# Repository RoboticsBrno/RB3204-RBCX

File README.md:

# RB3204-RBCX

<p align="center">

</p>

RBCX is a universal controller for hobby robots. It is a successor of [RB3201-RBControl](https://github.com/RoboticsBrno/RB3201-RBControl).
It is used in our robot [Robotka](https://robotka.robotickytabor.cz) on [Robo camp 2020](https://robotickytabor.cz).

<div align="center">
  	<td></td>
	<td></td>
</div>

## Features
- 4 DC motors with encoders
- 4 servos with feedback (via ADC)
- 4 LEDs
- buttons with the gamepad interface
- Smart Servo connector
- piezo buzzer
- RTC
- ultra-sonic distance sensor connector
- I2C connectors
- OLED display connector
- accelerometer and gyroscope
- micro USB and USB-C connectors
- battery connector (without charging circuit)

## Hardware
Board is based on `STM32F103VC` microcontroller and `ESP32-DevKitC`.

STM32 is used for motor control and other low-level tasks.
ESP32 is used for high-level tasks like communication with mobile app and sending commands to STM32 via UART.

### [STM32F103VC](https://www.st.com/en/microcontrollers-microprocessors/stm32f103vc.html)

-  72 MHz, 32bit ARM Cortex-M3
-  48 KiB RAM, 256 KiB Flash
-  5x UART, USB
-  Debug support (with ST-Link)
-  Programmable in C++, with FreeRTOS and stm32cube framework, in Platform.io
-  Our [bootloader](https://github.com/RoboticsBrno/sboot_stm32) based on [sboot_stm32](https://github.com/dmitrystu/sboot_stm32).

### [ESP32-DevKitC](https://www.espressif.com/en/products/devkits/esp32-devkitc)

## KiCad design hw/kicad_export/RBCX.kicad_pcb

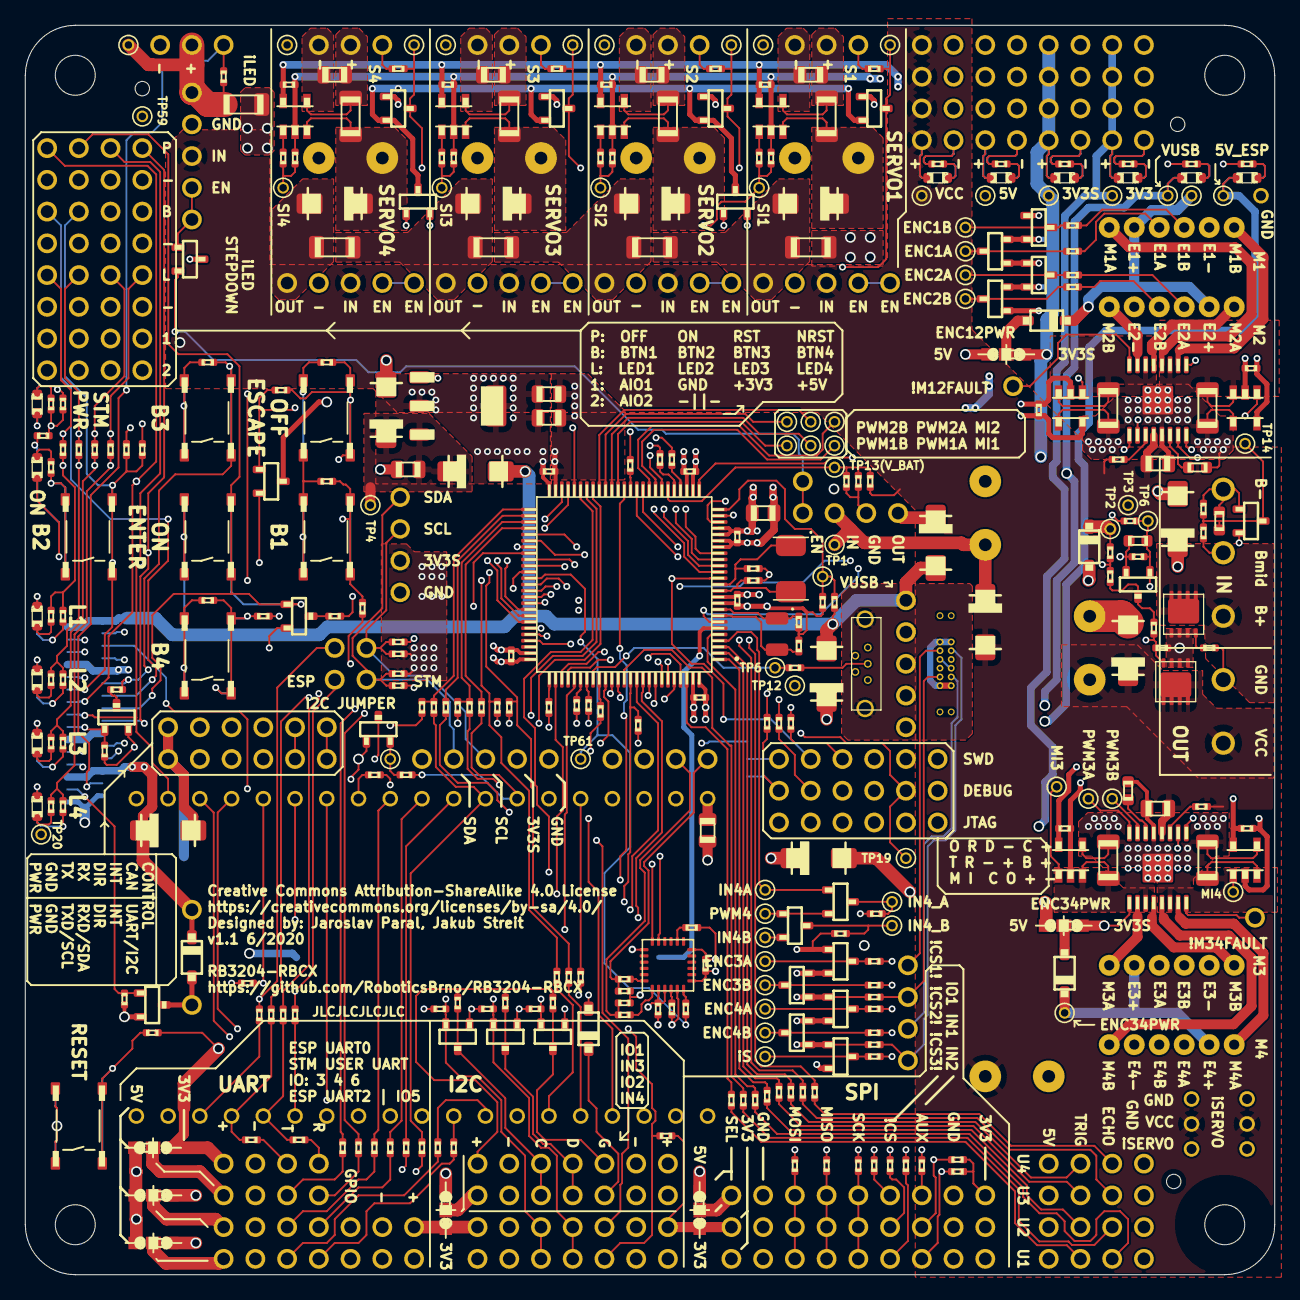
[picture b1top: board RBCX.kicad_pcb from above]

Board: 4 copper layers, 100.0 x 100.0 mm, 470 parts (0 on the bottom side), 294 nets.

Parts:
@HOLE0, @HOLE1, @HOLE2, @HOLE3, @HOLE4, @HOLE5, @HOLE6: (no value)
B1: PIEZO
BAT1: CR2032; SMD-BAT-CR2032-BS-6-1
C1, C2, C24, C25, C26, C27, C40: 220u; E5-10,5
C3, C4, C14, C19, C36, C37, C38, C39, C41, C51, C53: 10u; C0805
C5, C17, C18, C22, C23, C28, C29, C30, C31, C43, C44, C46, C47, C48, C49, C50, C52: 100n; C0402
C6, C8, C16, C21: 2u2; C0603
C7, C9, C10, C11, C12, C13, C32, C33, C34, C35: 1u; C0402
C15, C20, C42: 10n; C0402
C45: 2n2; C0402
C54, C56: 18p; C0402
C55, C57: 6.8p; C0402
D1, D10, D14, D15, D20: B5819W; SOD123
D2, D3, D4, D5, D6, D7, D8, D12, D29, D30, D31, D32, D38: SS34; SMA
D9, D16, D17, D18, D19, D22, D23, D24, D25, D33, D34, D35, D36, D37: BAS40-04; SOT23
D11, D13, D21, D26, D27, D28: BAS40-05; SOT23
IC1: AMS1117-3.3; SOT223
IC2, IC5: DRV8833PWP; HTSSOP
IC3, IC4, IC6, IC7, IC8, IC9, IC10, IC11: INA180A4; SOT23-5L
IC12: MPU-6050; QFN50P400X400X95-24N
IC13: STM32F103VCT6; QFP50P1600X1600X160-100N_STM32F103VCT6
IM1, IM2, IM5, IM6, IM7, IM8: STEPDOWN
IM3: DISPLAY-OLED-128X64-I2C-W_HOLES; DISPLAY-OLED-128X64-I2C_W-HOLES
IM4: DISPLAY-OLED-128X32
IM9: DEVKITC
JP1: 3V3_EN; 1X01
JP2: +3V3STM; 2X04
JP3: +3V3; 2X04
JP4: +5V; 2X04
JP5: VCC; 2X04
JP6: UTS1; 1X04
JP7: ESP_I2C1_VSEL; 1X04
JP8: ESP_SPI1; 1X06
JP9: ESP_UART; 1X04
JP10: ESP_I2C_AUX1_VSEL; 1X03
JP11: ESP_UART_AUX; 1X03
JP12: ESP_SPI_AUX1; 1X03
JP13: UTS2; 1X04
JP14: ESP_I2C2_VSEL; 1X04
JP15: ESP_SPI2; 1X06
JP16: UTS3; 1X04
JP17: ESP_I2C_AUX2_VSEL; 1X03
JP18: STM_UART; 1X04
JP19: ESP_SPI_AUX2; 1X03
JP20: UTS4; 1X04
JP21: ESP_SPI3; 1X06
JP22: ESP_I2C1; 1X04
JP23: ESP_UCOM; 1X04
JP24: ESP_SPI_AUX3; 1X03
JP25: ESP_I2C_AUX1; 1X03
JP26: ESP_UCOM_AUX; 1X03
JP27: ILED_EN; 1X01
JP28: ESP_I2C2; 1X04
JP29: AIO; 2X04
JP30: ESP_I2C_AUX2; 1X03
JP31: ILED; 1X03
JP32: USB; 1X05
JP33: SWD; 1X06
JP34: DEBUG; 1X04
JP35: USBC_AUX; 1X04
JP36: BOOT_SW; 1X02
JP37: ESP32_JTAG; 1X06
JP38: MPU_I2C; 1X04
JP39: EXPANDER_UART; 1X06
JP40: ESP_PROG_UART; 1X04
JP41: EXPANDER_CAN/I2C; 1X06
JP42: LEDS; 2X04
JP43: BUTTONS; 2X04
JP44: BUZZER; 1X01
JP45: PWR_BUTTONS; 2X04
JP46: M12FAULT; 1X01
JP47: M34FAULT; 1X01
JP48: SERVO1_EN; 1X01
JP49: SERVO2_EN; 1X01
JP50: SERVO3_EN; 1X01
JP51: SERVO4_EN; 1X01
JP52: SERVO1; 1X03
JP53: SERVO2; 1X03
JP54: SERVO3; 1X03
JP55: SERVO4; 1X03
JP56: INTELIGENT_SERVO1; 292161-3
JP57: INTELIGENT_SERVO2; 292161-3
JP58: I2C_INTERCONNECT; 2X02
LED1, LED2, LED3, LED4, LED5, LED6, LED7, LED8, LED9, LED10, LED11, LED12, LED17, LED18, LED21, LED22, LED23, LED24: red; CHIPLED_0603
LED13, LED14: green; CHIPLED_0603
LED15, LED16: yellow; CHIPLED_0603
LED19, LED20: blue; CHIPLED_0603
P1: M1; JST-PH6
P2: M2; JST-PH6
P3: M3; JST-PH6
P4: M4; JST-PH6
Q1, Q2: NCE20P45Q; MLP3.3X3.3_HS
Q3, Q4, Q5, Q6, Q7, Q8, Q9, Q10: 2N7002; SOT23
R1, R51, R57, R75: 100k; R0402
R2, R4, R6, R10, R11, R71, R124, R125: 10k; R0402
R3, R8: 24k; R0402
R5, R26, R27, R28, R29, R30, R31, R32, R33, R34, R35, R36, R39, R40, R41, R44, R45, R46, R47, R48, R49, R52, R53, R54, R55, R56, R58, R59, R60, R61, R65, R66, R68, R69, R72, R73, R74, R80, R81, R82, R83, R84, R85, R86, R87, R88, R89, R90, R91, R92, R93, R94, R95, R96, R97, R98, R99, R100, R101, R103, R104, R105, R106, R108, R145, R146, R147, R148, R149, R150, R151, R152, R153, R156, R157: 330R; R0402
R7, R107, R109: 1M; R0402
R9, R70: 5k6; R0402
R12, R13, R24, R25, R37, R38, R42, R43, R50, R62, R64, R78, R79, R110, R111, R154, R155: 4k7; R0402
R14, R15, R102, R114, R115, R116, R117, R120, R121, R122, R123, R140, R141, R142, R143, R144: 2k2; R0402
R16, R17, R18, R19, R20, R21, R22, R23, R76, R77, R112, R113, R132, R134, R136, R138: 1k; R0402
R63, R128, R129, R130, R131: 0R; R1206
R67: 1k5; R0402
R118, R119, R126, R127, R133, R135, R137, R139: 5m; R1206
S1, S2, S3, S4, S5, S6, S7, S8, S9, S10, S11, S12, S13, S14: CHOOSE_ME; TS-1187A
SJ1, SJ2, SJ3, SJ4, SJ5, SJ8, SJ9: SJ_2_DEFAULT
SJ6, SJ7: SJ_2_0603
TP1, TP2, TP3, TP4, TP5, TP6, TP7, TP8, TP9, TP10, TP12, TP13, TP14, TP15, TP16, TP17, TP18, TP19, TP20, TP21, TP22, TP23, TP24, TP25, TP26, TP27, TP28, TP29, TP30, TP31, TP32, TP33, TP34, TP35, TP36, TP37, TP38, TP39, TP40, TP41, TP42, TP43, TP44, TP45, TP46, TP47, TP48, TP49, TP50, TP51, TP52, TP53, TP54, TP55, TP56, TP57, TP58, TP59, TP60, TP61: TP_06
TP11: TP_08
X1: POWER_IN; W237-133
X2: POWER_OUT; W237-132
X3: 52559-3092
X4: uUSB; 614105150621
X5: USB_C_VERT_THT_8PIN
Y1: 5032/2P; OSCCC500X320X135
Y2: 3215_2P; SMD-3215_2P

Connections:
3V3_EN: D11.2, IM1.EN, JP1.1
3V3_IN: C3.2, D6.C, D7.C, IC1.3, TP4.P$1
5V_IN: C2.+, D4.C, IM1.IN, TP1.P$1
+3V3: IM9.1, JP3.1, JP3.3, JP3.5, JP3.7, JP11.3, JP12.3, JP15.1, JP19.3, JP21.1, JP22.1, JP24.3, JP25.3, JP26.3, JP28.1, JP30.3, JP37.5, LED7.A, LED8.A, Q5.1, Q6.1, Q7.1, R24.2, R37.2, R42.2, R50.1, R51.1, R57.1, R62.1, SJ1.3, SJ2.3, SJ3.1, SJ5.1, TP10.P$1
+3V3S: C4.2, C17.1, C18.1, C22.1, C23.1, C28.1, C29.1, C30.1, C31.1, C42.1, C43.2, C46.2, C47.2, C48.2, C49.2, C50.2, C51.2, C52.2, C53.2, D9.2, D11.3, D13.3, D16.2, D17.2, D18.2, D19.2, D22.2, D23.2, D24.2, D25.2, D27.3, D28.3, D33.2, D34.2, D35.2, D36.2, D37.2, IC1.2, IC1.4, IC2.1, IC3.5, IC4.5, IC5.1, IC6.5, IC7.5, IC8.5, IC9.5, IC10.5, IC11.5, IC12.8, IC12.9, IC12.13, IC13.11, IC13.21, IC13.22, IC13.28, IC13.50, IC13.75, IC13.100, IM3.2, IM4.2, JP2.1, JP2.3, JP2.5, JP2.7, JP29.5, JP29.6, JP33.1, JP34.1, JP36.1, JP38.1, JP40.1, LED5.A, LED6.A, LED23.A, LED24.A, R6.2, R78.2, R79.2, R107.2, R154.2, R155.2, SJ4.3, SJ7.1, SJ8.1, SJ9.1, TP9.P$1, X3.11, X3.12
+5V: B1.+, D1.A, D5.C, D6.A, D12.C, D14.C, D38.A, IM1.OUT, JP4.1, JP4.3, JP4.5, JP4.7, JP6.1, JP13.1, JP16.1, JP20.1, JP29.7, JP29.8, LED3.A, LED4.A, R63.2, R128.1, SJ1.1, SJ2.1, SJ3.3, SJ4.1, SJ5.3, SJ7.3, SJ8.3, SJ9.3, TP8.P$1, X3.5, X3.6
BAT+: Q1.5, Q1.6, Q1.7, Q1.8, Q1.9, X1.3
BAT+_PROTECTED: D1.C, D2.C, Q1.1, Q1.2, Q1.3, Q2.1, Q2.2, Q2.3, R1.1, R3.2, TP2.P$1
BAT_MID: R9.2, X1.2
BOOT0: IC13.94, JP36.2, Q9.1, R75.1, TP19.P$1, X3.13
BOOT1_PULL-DOWN: Q9.3, R74.1
BUTTON1: IC13.97, R90.1
BUTTON2: IC13.57, R93.1
BUTTON3: IC13.37, R96.1
BUTTON4: IC13.58, R100.1
BUTTON-1: C13.1, JP43.1, R90.2, S3.C, S3.D, S4.C, S4.D, X3.18
BUTTON-2: C12.1, JP43.3, R93.2, S5.C, S5.D, S6.C, S6.D, X3.19
BUTTON-3: C11.1, JP43.5, R74.2, R96.2, S7.C, S7.D, S8.C, S8.D, X3.20
BUTTON-4: C10.1, JP43.7, R100.2, S9.C, S9.D, S10.C, S10.D, X3.21
BUTTON-OFF: C9.1, JP45.1, R102.2, S11.C, S11.D, S12.C, S12.D, X3.17
BUTTON-ON: C5.2, JP45.3, Q3.1, R3.1, S1.C, S1.D, S2.C, S2.D, X3.16
BUTTON-ON-LV: Q3.3, R5.2
BUTTON_OFF: D13.1, IC13.46, R102.1
BUTTON_ON: IC13.61, R5.1
BUZZER: IC13.84, R108.1
BUZZER-: B1.-, D14.A, Q10.3
BUZZER-GATE: JP44.1, Q10.1, R108.2, R109.1, X3.3
CONTROL-DIR: JP39.5, JP41.5, R84.2
CONTROL-INT: JP39.6, JP41.6, R85.2
CONTROL-RX/SDA: JP39.4, R83.2
CONTROL-TX/SCL: JP39.3, R82.2
CONTROL_RX/SDA: D17.3, IC13.60, R115.1, TP27.P$1
CONTROL_TX/SCL: IC13.48, R83.1, R145.2
CPOUT: C45.2, IC12.20
DEBUG-RX: JP34.3, R72.2
DEBUG-TX: JP34.4, R73.2, SJ6.1
DEBUG_RX: IC13.79, R72.1
DEBUG_TX: IC13.78, R73.1
ENC1A: D16.3, IC13.59, R114.1, TP26.P$1
ENC1B: D23.3, IC13.89, R69.1, R121.1, TP41.P$1
ENC2A: D18.3, IC13.23, R116.1, TP28.P$1
ENC2B: D19.3, IC13.24, R117.1, TP29.P$1
ENC3A: D22.3, IC13.77, R120.1, TP40.P$1
ENC3B-SWO: R69.2, SJ6.3
ENC4A: D24.3, IC13.90, R122.1, TP42.P$1
ENC4B: D25.3, IC13.91, R123.1, TP43.P$1
ENC12PWR: D15.C, P1.5, P2.5, TP21.P$1
ENC12_PWR: IC13.47, R82.1, R146.2
ENC34PWR: D20.C, P3.5, P4.5, TP32.P$1
ENC34_PWR: D20.A, SJ9.2
ENC_1A: P1.4, R114.2
ENC_1B: P1.3, R115.2
ENC_2A: P2.4, R116.2
ENC_2B: P2.3, R117.2
ENC_3A: P3.4, R120.2
ENC_3B: P3.3, R121.2
ENC_4A: P4.4, R122.2
ENC_4B: P4.3, R123.2
ESP-I2C-PWR: JP7.1, JP10.3, JP14.1, JP17.3, R25.2, R38.2, R43.2, SJ2.2
ESP-I2C-SCL: JP22.3, JP28.3, JP58.3, Q5.2, R24.1, R29.2
ESP-I2C-SCL-VSEL: JP7.3, JP14.3, Q5.3, R25.1
ESP-I2C-SDA: JP22.4, JP28.4, JP58.1, Q6.2, R37.1, R41.2
ESP-I2C-SDA-VSEL: JP7.4, JP14.4, Q6.3, R38.1
ESP-SPI-MISO: JP8.4, JP15.4, JP21.4, R30.2
ESP-SPI-MOSI: JP8.3, JP15.3, JP21.3, R28.2
ESP-SPI-SCK: JP8.5, JP15.5, JP21.5, R32.2
ESP-SPI-~CS1: JP8.6, R34.2
ESP-SPI-~CS2: JP15.6, R46.2
ESP-SPI-~CS3: JP21.6, R54.2
ESP-UART-RX: JP40.4, R87.2
ESP-UART-TX: JP40.3, R86.2
ESP-USART-RX: JP9.3, R31.2
ESP-USART-TX: JP9.4, R33.2
ESP_+5V: C41.2, D8.C, D38.C, IM9.19, LED11.A, LED12.A, TP60.P$1
ESP_EN: D13.2, IC13.85, IM9.2, JP45.5, Q8.1, R107.1, S13.C, S13.D, S14.C, S14.D, TP59.P$1, X3.15
ESP_SPI_PWR: JP8.1, SJ1.2
ESP_UCOM_PWR: JP23.1, SJ5.2
ESP_USART_PWR: JP9.1, SJ3.2
EXPANDER_COM_PWR: D12.A, JP39.1, JP41.1, SJ7.2, TP20.P$1
EXPANDER_RX: IM9.25, R146.1
EXPANDER_TX: IM9.24, R145.1
GND: BAT1.VSS, C1.-, C2.-, C3.1, C4.1, C6.2, C7.2, C8.2, C9.2, C10.2, C11.2, C12.2, C13.2, C14.2, C16.2, C17.2, C18.2, C19.2, C21.2, C22.2, C23.2, C24.-, C25.-, C26.-, C27.-, C28.2, C29.2, C30.2, C31.2, C32.2, C33.2, C34.2, C35.2, C36.1, C37.1, C38.1, C39.1, C40.-, C41.1, C42.2, C43.1, C44.1, C45.1, C46.1, C47.1, C48.1, C49.1, C50.1, C51.1, C52.1, C53.1, C54.1, C55.1, C56.1, C57.1, D3.A, D9.1, D16.1, D17.1, D18.1, D19.1, D22.1, D23.1, D24.1, D25.1, D33.1, D34.1, D35.1, D36.1, D37.1, IC1.1, IC2.13, IC2.GND, IC3.2, IC3.4, IC4.2, IC4.4, IC5.13, IC5.GND, IC6.2, IC6.4, IC7.2, IC7.4, IC8.2, IC9.2, IC10.2, IC11.2, IC12.1, IC12.11, IC12.18, IC13.10, IC13.19, IC13.20, IC13.27, IC13.49, IC13.74, IC13.99, IM1.GND, IM2.GND, IM3.1, IM4.1, IM5.GND, IM6.GND, IM7.GND, IM8.GND, IM9.14, IM9.32, IM9.38, JP2.2, JP2.4, JP2.6, JP2.8, JP3.2, JP3.4, JP3.6, JP3.8, JP4.2, JP4.4, JP4.6, JP4.8, JP5.2, JP5.4, JP5.6, JP5.8, JP6.4, JP7.2, JP8.2, JP9.2, JP10.2, JP11.2, JP12.2, JP13.4, JP14.2, JP15.2, JP16.4, JP17.2, JP18.2, JP19.2, JP20.4, JP21.2, JP22.2, JP23.2, JP24.2, JP25.2, JP26.2, JP28.2, JP29.3, JP29.4, JP30.2, JP31.3, JP32.5, JP33.3, JP34.2, JP37.6, JP38.2, JP39.2, JP40.2, JP41.2, JP42.2, JP42.4, JP42.6, JP42.8, JP43.2, JP43.4, JP43.6, JP43.8, JP45.2, JP45.4, JP45.6, JP45.8, JP52.3, JP53.3, JP54.3, JP55.3, JP56.3, JP57.3, LED13.C, LED14.C, LED15.C, LED16.C, LED17.C, LED18.C, LED19.C, LED20.C, P1.2, P2.2, P3.2, P4.2, Q3.2, Q4.2, Q9.2, Q10.2, R2.1, R7.1, R10.1, R11.1, R12.1, R13.1, R14.1, R15.1, R16.1, R17.1, R18.1, R19.1, R20.1, R21.1, R22.1, R23.1, R71.1, R75.2, R76.2, R77.2, R109.2, R110.1, R111.1, R112.1, R113.1, R118.1, R119.1, R124.1, R125.1, R126.1, R127.1, S1.A, S1.B, S2.A, S2.B, S3.A, S3.B, S4.A, S4.B, S5.A, S5.B, S6.A, S6.B, S7.A, S7.B, S8.A, S8.B, S9.A, S9.B, S10.A, S10.B, S11.A, S11.B, S12.A, S12.B, S13.A, S13.B, S14.A, S14.B, TP11.P$1, X1.1, X2.1, X3.22, X3.23, X4.5, X5.A1, X5.A12, X5.B1, X5.B12
GND_SEPARATOR: D15.A, SJ8.2
GPIO1: IM9.7, R36.1
GPIO2: IM9.8, R58.1
GPIO3: IM9.9, R55.1
GPIO4: IM9.10, R56.1
GPIO5: IM9.11, R35.1
GPIO6/TMS: IM9.12, JP37.1, R59.1, R149.1
GPIO7/TCK: IM9.15, JP37.3, R45.1, R150.1
GPIO-1: JP12.1, R36.2
GPIO-1-VSEL: JP10.1, Q7.3, R43.1
GPIO-2: JP25.1, R58.2, X3.26
GPIO-3: JP23.3, R55.2
GPIO-4: JP23.4, R56.2
GPIO-5: JP11.1, R35.2
GPIO-6: JP26.1, R59.2
GPIO-7: Q7.2, R42.1, R45.2
I2C_SCL: IM9.36, R29.1
I2C_SDA: IM9.33, R41.1
ILED: Q8.2, R65.2, TP16.P$1
ILED-5V: JP31.1, Q8.3, R64.1, X3.4
ILED_EN: D11.1, IM2.EN, JP27.1
ILED_PWR: IM2.OUT, JP31.2, R63.1, R64.2, TP15.P$1
IN1: IM9.3, JP19.1, R51.2
IN2: IM9.4, JP24.1, R57.2
IN3: D10.A, IM9.5, R50.2
IN3-5V: D10.C, JP17.1
IN4: IM9.6, JP30.1, R62.2
IN4A: D21.1, IC13.4, TP35.P$1
IN4B: D26.2, IC13.38, TP37.P$1
IN4_A: D21.3, IC5.9, R125.2, TP38.P$1
IN4_B: D26.3, IC5.10, R124.2, TP39.P$1
INTELLIGENT_SERVO: D37.3, IC13.80, R144.1, TP58.P$1
ISERVO: JP56.1, JP57.1, R144.2
I_LED/TDI: IM9.13, JP37.2, R65.1, R151.1
LED1: IC13.32, R91.1, R92.1, R103.1
LED2: IC13.67, R94.1, R95.1, R104.1
LED3: IC13.68, R97.1, R98.1, R105.1
LED4: IC13.69, R99.1, R101.1, R106.1
LED-1: JP42.1, R103.2, X3.7
LED-2: JP42.3, R104.2, X3.8
LED-3: JP42.5, R105.2, X3.9
LED-4: JP42.7, R106.2, X3.10
LED_1: LED13.A, R91.2
LED_1B: LED14.A, R92.2
LED_2: LED15.A, R94.2
LED_2B: LED16.A, R95.2
LED_3: LED17.A, R97.2
LED_3B: LED18.A, R98.2
LED_4: LED19.A, R99.2
LED_4B: LED20.A, R101.2
M1A: IC2.4, P1.6
M1B: IC2.2, P1.1
M1GND: IC2.3, IC3.3, R118.2
M2A: IC2.5, P2.6
M2B: IC2.7, P2.1
M2GND: IC2.6, IC4.3, R119.2
M3A: IC5.2, P3.6
M3B: IC5.4, P3.1
M3GND: IC5.3, IC6.3, R126.2
M4A: IC5.7, P4.6
M4B: IC5.5, P4.1
M4GND: IC5.6, IC7.3, R127.2
MI1: IC3.1, IC13.33, TP30.P$1
MI2: IC4.1, IC13.34, TP31.P$1
MI3: IC6.1, IC13.35, TP44.P$1
MI4: IC7.1, IC13.36, TP45.P$1
MPU-INT: IC12.12, R153.2
MPU-SCL: JP38.3, R78.1, R80.1
MPU-SDA: JP38.4, R79.1, R81.1
MPU_INT: IC13.62, R153.1, TP61.P$1
MPU_SCL: IC12.7, R80.2
MPU_SDA: IC12.6, R81.2
NRST: IC13.14, JP33.5, JP45.7, X3.14
OSC32_IN: C55.2, IC13.8, Y2.2
OSC32_OUT: C57.2, IC13.9, Y2.1
OSC_IN: C54.2, IC13.12, Y1.2
OSC_OUT: C56.2, IC13.13, Y1.1
POWER: C6.1, IC13.7, Q4.1, R6.1, R7.2, TP6.P$1
PROT_GATE: Q1.4, R2.2
PWM1A: IC2.15, IC13.40, TP23.P$1
PWM1B: IC2.16, IC13.39, TP22.P$1
PWM2A: IC2.10, IC13.42, TP25.P$1
PWM2B: IC2.9, IC13.41, TP24.P$1
PWM3A: IC5.16, IC13.44, TP33.P$1
PWM3B: IC5.15, IC13.43, TP34.P$1
PWM4: D21.2, D26.1, IC13.45, TP36.P$1
PWRLED_+3V3: LED7.C, R18.2
PWRLED_+3V3B: LED8.C, R19.2
PWRLED_+3V3S: LED5.C, R16.2
PWRLED_+3V3S1: LED23.C, R112.2
PWRLED_+3V3S_B: LED6.C, R17.2
PWRLED_+3V3S_B1: LED24.C, R113.2
PWRLED_+5V: LED3.C, R14.2
PWRLED_+5VESP: LED11.C, R22.2
PWRLED_+5VESP_B: LED12.C, R23.2
PWRLED_+5V_B: LED4.C, R15.2
PWRLED_VCC: LED1.C, R12.2
PWRLED_VCC1: LED21.C, R110.2
PWRLED_VCC_B: LED2.C, R13.2
PWRLED_VCC_B1: LED22.C, R111.2
PWRLED_VUSB: LED9.C, R20.2
PWRLED_VUSB_B: LED10.C, R21.2
PWRSW: C5.1, Q4.3, R4.1
PWRSW_GATE: Q2.4, R1.2, R4.2, TP3.P$1
REGOUT: C44.2, IC12.10
SERVO1: D33.3, IC13.63, R140.1, TP54.P$1
SERVO1PWR: D29.A, IM5.OUT, R128.2, R129.1
SERVO1_EN: D27.2, IM5.EN, JP48.1
SERVO1_PWR: C24.+, D29.C, IC8.3, R133.2
SERVO2: D34.3, IC13.64, R141.1, TP55.P$1
SERVO2PWR: D30.A, IM6.OUT, R129.2, R130.1
SERVO2_EN: D27.1, IM6.EN, JP49.1
SERVO2_PWR: C25.+, D30.C, IC9.3, R135.2
SERVO3: D35.3, IC13.65, R142.1, TP56.P$1
SERVO3PWR: D31.A, IM7.OUT, R130.2, R131.1
SERVO3_EN: D28.2, IM7.EN, JP50.1
SERVO3_PWR: C26.+, D31.C, IC10.3, R137.2
SERVO4: D36.3, IC13.66, R143.1, TP57.P$1
SERVO4PWR: D32.A, IM8.OUT, R131.2
SERVO4_EN: D28.1, IM8.EN, JP51.1
SERVO4_PWR: C27.+, D32.C, IC11.3, R139.2
SERVO_1: JP52.1, R140.2
SERVO_1_PWR: C36.2, IC8.4, JP52.2, R133.1, TP50.P$1
SERVO_2: JP53.1, R141.2
SERVO_2_PWR: C37.2, IC9.4, JP53.2, R135.1, TP51.P$1
SERVO_3: JP54.1, R142.2
SERVO_3_PWR: C38.2, IC10.4, JP54.2, R137.1, TP52.P$1
SERVO_4: JP55.1, R143.2
SERVO_4_PWR: C39.2, IC11.4, JP55.2, R139.1, TP53.P$1
SI1: C32.1, IC13.18, R132.1, TP46.P$1
SI2: C33.1, IC13.17, R134.1, TP47.P$1
SI3: C34.1, IC13.16, R136.1, TP48.P$1
SI4: C35.1, IC13.15, R138.1, TP49.P$1
SI_1: IC8.1, R132.2
SI_2: IC9.1, R134.2
SI_3: IC10.1, R136.2
SI_4: IC11.1, R138.2
SPI_MISO: IM9.31, R30.1
SPI_MOSI: IM9.37, R28.1
SPI_SCK: IM9.30, R32.1
SPI_~SS1: IM9.29, R34.1
SPI_~SS2: IM9.26, R46.1
SPI_~SS3~/TDO: IM9.23, JP37.4, R54.1, R152.1
STM-AIO1: JP29.1, R60.2
STM-AIO2: JP29.2, R61.1
STM-CAN-RX: JP41.4, R89.2
STM-CAN-TX: JP41.3, R88.2
STM-I2C-SCL: IC12.23, IM3.3, IM4.3, JP58.4, R155.1, R157.2, X3.25
STM-I2C-SDA: IC12.24, IM3.4, IM4.4, JP58.2, R154.1, R156.2, X3.24
STM-UART-RX: JP18.4, R49.2
STM-UART-TX: JP18.3, R48.2
STM_AIO1: IC13.29, R60.1
STM_AIO2: IC13.30, R61.2
STM_CAN_RX: IC13.81, R89.1
STM_CAN_TX: IC13.82, R88.1
STM_I2C_SCL: IC13.95, R157.1
STM_I2C_SDA: IC13.96, R156.1
STM_SPI_MISO: IC13.53, R85.1, R152.2
STM_SPI_MOSI: IC13.54, R151.2
STM_SPI_SCK: IC13.52, R150.2
STM_SPI_~CS: IC13.51, R84.1, R149.2
STM_UART_PWR: JP18.1, SJ4.2
SWCLK: IC13.76, R66.1
SWCLK_: JP33.2, R66.2
SWDIO: IC13.72, R68.1
SWDIO_: JP33.4, R68.2
SWO: JP33.6, SJ6.2
TUNNEL_RX: IC13.87, R147.2
TUNNEL_TX: IC13.86, R148.2
UART2_RX: IM9.27, R31.1
UART2_TX: IM9.28, R33.1
UART_RX: IM9.34, R87.1, R148.1
UART_TX: IM9.35, R86.1, R147.1
USB_CC1: JP35.2, R77.1, X5.A5
USB_CC2: JP35.4, R76.1, X5.B5
USB_DM: IC13.70, JP32.2, X3.28, X4.2, X5.A7, X5.B7
USB_DP: IC13.71, JP32.3, R67.2, X3.27, X4.3, X5.A6, X5.B6
USB_DP_PULLUP: IC13.83, R67.1, TP17.P$1
USB_ID: JP32.4, X4.4
USB_SBU1: JP35.1, X5.A8
USB_SBU2: JP35.3, X5.B8
USB_SHIELD: X4.S1, X4.S2
USER_RX: IC13.93, R49.1
USER_TX: IC13.92, R48.1
UTS1-ECHO: JP6.3, R27.2
UTS1-TRIG: JP6.2, R26.2
UTS1_ECHO: IC13.5, R27.1
UTS1_TRIG: IC13.98, R26.1
UTS2-ECHO: JP13.3, R40.2
UTS2-TRIG: JP13.2, R39.2
UTS2_ECHO: IC13.88, R40.1
UTS2_TRIG: IC13.1, R39.1
UTS3-ECHO: JP16.3, R47.2
UTS3-TRIG: JP16.2, R44.2
UTS3_ECHO: IC13.55, R47.1
UTS3_TRIG: IC13.2, R44.1
UTS4-ECHO: JP20.3, R53.2
UTS4-TRIG: JP20.2, R52.2
UTS4_ECHO: IC13.56, R53.1
UTS4_TRIG: IC13.3, R52.1
VBAT: BAT1.VBAT, IC13.6, TP12.P$1
VCC: C1.+, C14.1, C15.1, C19.1, C20.1, C40.+, D3.C, D4.A, IC2.12, IC5.12, IM2.IN, IM5.IN, IM6.IN, IM7.IN, IM8.IN, JP5.1, JP5.3, JP5.5, JP5.7, JP56.2, JP57.2, LED1.A, LED2.A, LED21.A, LED22.A, Q2.5, Q2.6, Q2.7, Q2.8, Q2.9, R8.2, TP7.P$1, X2.2, X3.1, X3.2
VCP12: C15.2, IC2.11
VCP34: C20.2, IC5.11
VINT12: C16.1, IC2.14
VINT34: C21.1, IC5.14
VUSB: D2.A, D5.A, D7.A, D8.A, JP32.1, LED9.A, LED10.A, R70.2, TP5.P$1, X3.29, X3.30, X4.1, X5.A4, X5.A9, X5.B4, X5.B9
VUSB_DET: IC13.25, R70.1, R71.2, TP18.P$1
V_BAT: C7.1, IC13.31, R8.1, R10.2, TP13.P$1
V_BAT/2: C8.1, D9.3, IC13.26, R9.1, R11.2, TP14.P$1
~M12_FAULT: IC2.8, JP46.1
~M34_FAULT: IC5.8, JP47.1

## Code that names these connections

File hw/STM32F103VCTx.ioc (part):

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Mcu.Name=STM32F103V(C-D-E)Tx
Mcu.Package=LQFP100
Mcu.UserName=STM32F103VCTx
PA0-WKUP.GPIOParameters=GPIO_Label
PA0-WKUP.GPIO_Label=SERVO1 (TIM5_CH1)
PA0-WKUP.Signal=S_TIM5_CH1
PA1.GPIOParameters=GPIO_Label
PA1.GPIO_Label=SERVO2 (TIM5_CH2)
PA1.Signal=S_TIM5_CH2
PA10.GPIOParameters=GPIO_Label
PA10.GPIO_Label=DEBUG (USART1_RX)
PA10.Mode=Asynchronous
PA10.Signal=USART1_RX
PA11.Mode=Device
PA11.Signal=USB_DM
PA12.Mode=Device
PA12.Signal=USB_DP
PA13.Signal=SYS_JTMS-SWDIO
PA14.Signal=SYS_JTCK-SWCLK
PA15.GPIOParameters=GPIO_Label
PA15.GPIO_Label=ENC1A (TIM2_CH1)
PA15.Signal=S_TIM2_CH1_ETR
PA2.GPIOParameters=GPIO_Label
PA2.GPIO_Label=SERVO3 (TIM5_CH3)
PA2.Signal=S_TIM5_CH3
PA3.GPIOParameters=GPIO_Label
PA3.GPIO_Label=SERVO4 (TIM5_CH4)
PA3.Signal=S_TIM5_CH4
PA4.GPIOParameters=GPIO_Label
PA4.GPIO_Label=AIO (DAC_OUT1/ADC2_IN4)
PA4.Signal=COMP_DAC1_group
PA5.GPIOParameters=GPIO_Label
PA5.GPIO_Label=AIO (DAC_OUT1/ADC2_IN5)
PA5.Signal=COMP_DAC2_group
PA6.GPIOParameters=GPIO_Label
PA6.GPIO_Label=VBAT (ADC2_IN6)
PA6.Signal=ADCx_IN6
PA7.GPIOParameters=GPIO_Label
PA7.GPIO_Label=VBAT/2 (ADC2_IN7)
PA7.Signal=ADCx_IN7
PA8.GPIOParameters=GPIO_Label
PA8.GPIO_Label=USB_DP_PULLUP
PA8.Signal=GPIO_Output
PA9.GPIOParameters=GPIO_Label
PA9.GPIO_Label=DEBUG (USART1_TX)
PA9.Mode=Asynchronous
PA9.Signal=USART1_TX
PB0.GPIOParameters=GPIO_Label
PB0.GPIO_Label=MI3 (ADC1_IN8)
PB0.Signal=ADCx_IN8
PB1.GPIOParameters=GPIO_Label
PB1.GPIO_Label=MI4 (ADC1_IN9)
PB1.Signal=ADCx_IN9
PB10.GPIOParameters=GPIO_Label
PB10.GPIO_Label=I2C_SCL
PB10.Signal=I2C2_SCL
PB11.GPIOParameters=GPIO_Label
PB11.GPIO_Label=I2C_SDA
PB11.Signal=I2C2_SDA
PB12.GPIOParameters=GPIO_Label
PB12.GPIO_Label=SPI_NSS/ESP_JTAG_TMS
PB12.Mode=NSS_Signal_Hard_Output
PB12.Signal=SPI2_NSS
PB13.GPIOParameters=GPIO_Label
PB13.GPIO_Label=SPI_SCK/ESP_JTAG_TCK
PB13.Mode=Full_Duplex_Master
PB13.Signal=SPI2_SCK
PB14.GPIOParameters=GPIO_Label
PB14.GPIO_Label=SPI_MISO/ESP_JTAG_TDO
PB14.Mode=Full_Duplex_Master
PB14.Signal=SPI2_MISO
PB15.GPIOParameters=GPIO_Label
PB15.GPIO_Label=SPI_MOSI/ESP_JTAG_TDI
PB15.Mode=Full_Duplex_Master
PB15.Signal=SPI2_MOSI
PB2.GPIOParameters=GPIO_PuPd,GPIO_Label
PB2.GPIO_Label=BUTTON3
PB2.GPIO_PuPd=GPIO_PULLUP
PB2.Signal=GPIO_Input
PB3.GPIOParameters=GPIO_Label
PB3.GPIO_Label=ENC1B (TIM2_CH2)
PB3.Signal=S_TIM2_CH2
PB4.GPIOParameters=GPIO_Label
PB4.GPIO_Label=ENC2A (TIM3_CH1)
PB4.Signal=S_TIM3_CH1
PB5.GPIOParameters=GPIO_Label
PB5.GPIO_Label=ENC2B (TIM3_CH2)
PB5.Signal=S_TIM3_CH2
PB6.GPIOParameters=GPIO_Label
PB6.GPIO_Label=BUTTON1
PB6.Signal=GPIO_Input
PB7.GPIOParameters=GPIO_Label
PB7.GPIO_Label=MPU_INT
PB7.Signal=GPIO_Input
PB8.GPIOParameters=GPIO_Label
PB8.GPIO_Label=CAN1_RX/I2C1_SCL
PB8.Signal=CAN_RX
PB9.GPIOParameters=GPIO_Label
PB9.GPIO_Label=CAN1_TX/I2C1_SDA
PB9.Signal=CAN_TX
PC0.GPIOParameters=GPIO_Label
PC0.GPIO_Label=SI1 (ADC3_IN10)
PC0.Signal=ADCx_IN10
PC1.GPIOParameters=GPIO_Label
PC1.GPIO_Label=SI2 (ADC3_IN11)
PC1.Signal=ADCx_IN11
PC10.GPIOParameters=GPIO_Label
PC10.GPIO_Label=ESP_COM (UART4_TX)
PC10.Mode=Asynchronous
PC10.Signal=UART4_TX
PC11.GPIOParameters=GPIO_Label
PC11.GPIO_Label=ESP_COM (UART4_RX)
PC11.Mode=Asynchronous
PC11.Signal=UART4_RX
PC12.GPIOParameters=GPIO_Label
PC12.GPIO_Label=ESP_PROG (UART5_TX)
PC12.Mode=Asynchronous
PC12.Signal=UART5_TX
PC13-TAMPER-RTC.GPIOParameters=GPIO_PuPd,GPIO_Label
PC13-TAMPER-RTC.GPIO_Label=VUSB_DET
PC13-TAMPER-RTC.GPIO_PuPd=GPIO_PULLUP
PC13-TAMPER-RTC.Signal=GPIO_Input
PC14-OSC32_IN.Mode=LSE-External-Oscillator
PC14-OSC32_IN.Signal=RCC_OSC32_IN
PC15-OSC32_OUT.Mode=LSE-External-Oscillator
PC15-OSC32_OUT.Signal=RCC_OSC32_OUT
PC2.GPIOParameters=GPIO_Label
PC2.GPIO_Label=SI3 (ADC3_IN12)
PC2.Signal=ADCx_IN12
PC3.GPIOParameters=GPIO_Label
PC3.GPIO_Label=SI4 (ADC3_IN13)
PC3.Signal=ADCx_IN13
PC4.GPIOParameters=GPIO_Label
PC4.GPIO_Label=MI1 (ADC1_IN14)
PC4.Signal=ADCx_IN14
PC5.GPIOParameters=GPIO_Label
PC5.GPIO_Label=MI2 (ADC1_IN15)
PC5.Signal=ADCx_IN15
PC6.GPIOParameters=GPIO_Label
PC6.GPIO_Label=ENC4A (TIM8_CH1)
PC6.Signal=S_TIM8_CH1
PC7.GPIOParameters=GPIO_Label
PC7.GPIO_Label=ENC4B (TIM8_CH2)
PC7.Signal=S_TIM8_CH2
PC8.GPIOParameters=GPIO_Label
PC8.GPIO_Label=ESP_EN
PC8.Signal=GPIO_Output
PC9.GPIOParameters=GPIO_Label
PC9.GPIO_Label=BUTTON_ON
PC9.Signal=GPIO_Output
PD0.GPIOParameters=GPIO_Label
PD0.GPIO_Label=IN4B
PD0.Signal=GPIO_Output
PD1.GPIOParameters=GPIO_Label
PD1.GPIO_Label=IN4A
PD1.Signal=GPIO_Output
PD10.GPIOParameters=GPIO_Label
PD10.GPIO_Label=LED1
PD10.Signal=GPIO_Output
PD11.GPIOParameters=GPIO_Label
PD11.GPIO_Label=LED2
PD11.Signal=GPIO_Output
PD12.GPIOParameters=GPIO_Label
PD12.GPIO_Label=ENC3A (TIM4_CH1)
PD12.Signal=S_TIM4_CH1
PD13.GPIOParameters=GPIO_Label
PD13.GPIO_Label=ENC3B (TIM4_CH2)
PD13.Signal=S_TIM4_CH2
PD14.GPIOParameters=GPIO_PuPd,GPIO_Label,GPIO_ModeDefaultOutputPP
PD14.GPIO_Label=LED3
PD14.GPIO_ModeDefaultOutputPP=GPIO_MODE_OUTPUT_OD
PD14.GPIO_PuPd=GPIO_NOPULL
PD14.Signal=GPIO_Output
PD15.GPIOParameters=GPIO_Label,GPIO_ModeDefaultOutputPP
PD15.GPIO_Label=LED4
PD15.GPIO_ModeDefaultOutputPP=GPIO_MODE_OUTPUT_OD
PD15.Signal=GPIO_Output
PD2.GPIOParameters=GPIO_Label
PD2.GPIO_Label=ESP_PROG (UART5_RX)
PD2.Mode=Asynchronous
PD2.Signal=UART5_RX
PD3.GPIOParameters=GPIO_Label
PD3.GPIO_Label=BUTTON2
PD3.Signal=GPIO_Input
PD4.GPIOParameters=GPIO_Label
PD4.GPIO_Label=BUTTON3
PD4.Signal=GPIO_Input
PD5.Mode=Asynchronous
PD5.Signal=USART2_TX
PD6.Mode=Asynchronous
PD6.Signal=USART2_RX
PD7.GPIOParameters=GPIO_Label
PD7.GPIO_Label=BUZZER
PD7.Signal=GPIO_Output
PD8.GPIOParameters=GPIO_Label
PD8.GPIO_Label=INTELLIGENT_SERVO
PD8.Signal=USART3_TX
PD9.GPIOParameters=GPIO_Label
PD9.GPIO_Label=POWER
PD9.Signal=GPIO_Output
PE0.GPIOParameters=GPIO_Label
PE0.GPIO_Label=UTS1_TRIG
PE0.Signal=GPIO_Output
PE1.GPIOParameters=GPIO_PuPd,GPIO_Label,GPIO_ModeDefaultEXTI
PE1.GPIO_Label=UTS1_ECHO
PE1.GPIO_ModeDefaultEXTI=GPIO_MODE_IT_RISING_FALLING
PE1.GPIO_PuPd=GPIO_PULLUP
PE1.Signal=GPXTI1
PE10.GPIOParameters=GPIO_Label
PE10.GPIO_Label=PWM2B (TIM1_CH2N)
PE10.Mode=PWM Generation2 CH2 CH2N
PE10.Signal=TIM1_CH2N
PE11.GPIOParameters=GPIO_Label
PE11.GPIO_Label=PWM2A (TIM1_CH2)
PE11.Signal=S_TIM1_CH2
PE12.GPIOParameters=GPIO_Label
PE12.GPIO_Label=PWM3B (TIM1_CH3N)
PE12.Mode=PWM Generation3 CH3 CH3N
PE12.Signal=TIM1_CH3N
PE13.GPIOParameters=GPIO_Label
PE13.GPIO_Label=PWM3A (TIM1_CH3)
PE13.Signal=S_TIM1_CH3
PE14.GPIOParameters=GPIO_Label
PE14.GPIO_Label=PWM4 (TIM1_CH4)
PE14.Signal=S_TIM1_CH4
PE15.GPIOParameters=GPIO_PuPd,GPIO_Label
PE15.GPIO_Label=BUTTON_OFF
PE15.GPIO_PuPd=GPIO_PULLUP
PE15.Signal=GPIO_Input
PE2.GPIOParameters=GPIO_Label
PE2.GPIO_Label=UTS2_TRIG
PE2.Signal=GPIO_Output
PE3.GPIOParameters=GPIO_PuPd,GPIO_Label,GPIO_ModeDefaultEXTI
PE3.GPIO_Label=UTS2_ECHO
PE3.GPIO_ModeDefaultEXTI=GPIO_MODE_IT_RISING_FALLING
PE3.GPIO_PuPd=GPIO_PULLUP
PE3.Signal=GPXTI3
PE4.GPIOParameters=GPIO_Label
PE4.GPIO_Label=UTS3_TRIG
PE4.Signal=GPIO_Output
PE5.GPIOParameters=GPIO_PuPd,GPIO_Label,GPIO_ModeDefaultEXTI
PE5.GPIO_Label=UTS3_ECHO
PE5.GPIO_ModeDefaultEXTI=GPIO_MODE_IT_RISING_FALLING
PE5.GPIO_PuPd=GPIO_PULLUP
PE5.Signal=GPXTI5
PE6.GPIOParameters=GPIO_Label
PE6.GPIO_Label=UTS4_TRIG
PE6.Signal=GPIO_Output
PE7.GPIOParameters=GPIO_PuPd,GPIO_Label
PE7.GPIO_Label=UTS4_ECHO
PE7.GPIO_PuPd=GPIO_PULLUP
PE7.Signal=GPIO_Input
PE8.GPIOParameters=GPIO_Label
PE8.GPIO_Label=PWM1B (TIM1_CH1N)
PE8.Mode=PWM Generation1 CH1 CH1N
PE8.Signal=TIM1_CH1N
PE9.GPIOParameters=GPIO_Label
PE9.GPIO_Label=PWM1A (TIM1_CH1)
PE9.Signal=S_TIM1_CH1
board=custom

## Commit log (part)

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2020-04-07 Add the CDC loopback demo, adjusted
2020-04-08 MainBoardBRD: change top side SMD parts footprint according IPC-7351 (using Library Expert Pro (2019.7) )
2020-04-11 Remove HID thing from USB
2020-04-12 Add bsp.hpp, add USART WIP
2020-04-13 Add DMA-enabled transmission for USART1
2020-04-15 MainBoard: 4 layers, motors connector, DRV8833, libraries
    - set 4 layers stack + change DRC setting about same signals, the rest is still same (possible place
    for improvements due to 4 layers stack and https://jlcpcb.com/capabilities/Capabilities)
    - motors connectors - remove terminal blocks, replace pinheads with JST-PH6 (2mm x 6 pins)
    - DRV8833
    - improve `DRV8833.lbr` library - fix thermal GND pad under the package
    - reroute on DPS and add thermal VIAs according http://www.ti.com/lit/an/slma004b/slma004b.pdf
2020-04-16 Fix fifo overrun
2020-04-18 MainBoard: Change power circuit to make ON button connected to GND
2020-04-18 MainBoard: Invalidate parts.xlsx
2020-04-18 MainBoardBRD: routing power - VCC, 5V, servo, DRV8833
2020-04-19 Add working cdc_uart_tunnel.cpp
2020-04-20 Fix PMA buffer overrun
2020-04-23 MainBoardBRD: routing
2020-04-24 Use polling for both CDC OUT and IN
2020-04-24 Increase primary UART RX ring buf size
2020-04-25 Apply formatting
2020-04-26 Fixup string descriptors
2020-04-26 Fix function name convention
2020-04-26 Fix pinInit()
2020-04-29 fw: add TravisCI config for rbcx-coprocessor project
2020-04-30 MainBoard: Add leds and uUSB to bottom side, move the leftmost pinheads far from the board edge, fix DRC error in DRV8833 library, swap position of servos and motors + power connectors
2020-05-02 MainBoard: Add power LEDs for VUSB and +5V_ESP and secondary power LEDS for +3v3S and VCC
2020-05-03 Fix function name convention
    Fix function name convention
    Fix method naming convention
    Fix pinInit()
    Fix cdcLinkPoll name
2020-05-03 Add basic docs
2020-05-05 TravisCI: change from Python 2.7 to 3.7
2020-05-05 Add doc for ByteFifo
2020-05-06 MainBoard: Swap IN4A and IN4B, routed motors + servos
2020-05-06 MainBoard: Fix USB connectors packages, add Design block backup file extensions to gitignore
2020-05-06 MainBoard: Mirror motor connectors (to the bottom side) and swap signals to keep previous routing
2020-05-06 MainBoard: Routing (coprocessor power), remove one output capacitor from LDO - shared with STM
2020-05-07 MainBoardBRD: Fix DRC errors
2020-05-07 MainBoardSCH: Reorder sheets and renumber parts
2020-05-07 MainBoardBRD: Mirror servos step-down enable pin
2020-05-07 MainBoardBRD: Add basic topside silkscreen
2020-05-08 MainBoardBRD: improve top and bottom silkscreen
2020-05-09 ele/hw: clean and refactor project structure
    - rename folder `ele` to `hw`
    - remove folder `MainBoard`
    - to folder `hw` add folders `lib`,`configuration` and `designBlock`
    - rename `RBCX-MainBoard{.brd/.sch}` to `RBCX{.brd/.sch}`
2020-05-11 hw: Add default V resistors, fix polygon Q1, prepare manufacturing data
    - add 0R resistors as default voltage selector for SJx
    - improve size of polygon for Q1 due to better cooling
    - prepare manufacturing data
    - renumber parts in schema
    - create `parts_SMT.xlsx` file with updated data
    - add CAM processor configuration
2020-05-11 MainBoardBRD: Add placeholder text for JLCPCB order number
2020-05-11 MainBoard: Swap PWM3A and PWM3B to maintain consistency
2020-05-11 MainBoardBRD: Remove SolderPaste from jumpers
2020-05-11 hwBRD: Improve silkscreen
    - silkscreen: fix motors JST connectors VCC/GND, update communication connectors
    - modify silkscreen of ESP32-DEVKITC in library `esp32.lbr`
2020-05-12 Unify clocksInit()
2020-05-13 Revert DRV8833-PWM-test
2020-05-15 Add control frame loopback
2020-05-17 Fix frame buffer size, hide ControlLink symbols from linker
2020-05-19 hw: clean `parts_SMT.xlsx`
2020-05-19 hw: create folder `RBCX_v1.0` with manufactured Eagle PCB files
2020-05-19 hwBRD: Fix R47 misplacement
2020-05-19 hwBRD: Fix SPI_SS3 and IN3 overlap
2020-05-21 hw_test: copy actual firmware from master
2020-05-22 hw_test: rename UARTs, add UARTs and their pins, systick interrupt blinks LED1 (not tested), add ST-LINK to platformio.ini
2020-05-23 fw: format whole code base with our `.clang-format`
    - add limit of 80 character per line to `.clang-format` file
    - format our files
    - src\*{.c/.cpp}
    - include\*{.h/.hpp}
    - add `formatOnSave` to VSCode setting
2020-05-23 Use encodeWithHeader
2020-05-23 Use MaxFrameSize instead of 257
2020-05-24 hw_test: fix tunnel spelling
2020-05-24 hw_test: USB test - redirected to debug USART, because of presence of DMA
2020-05-24 Format some files again after merge with master
2020-05-30 hw_test: buzzer test
2020-05-30 hw_test: RTC test - remove output pulse and add synchronization delay before printing
2020-06-02 hw_test: PWM test
2020-06-02 hw_test: PWM test: add explanation
2020-06-02 hw_test: fix broken Bsp.hpp from PWM test, add encoders
2020-06-03 hw_test: fix AFIO_MAPR write-only bits SWJ_CFG issue. DO NOT USE LL_GPIO_AF_*Remap* FUNCTIONS! Use LL_GPIO_AF_Remap instead.
2020-06-03 Add FreeRTOS files
2020-06-03 Remove forgotten prototype
2020-06-06 hw: update pinhead library
    - update pinhead library in RBCX design and modify the XML in `RBCX{.brp/.sch}` for correct import to KiCad
2020-06-06 Fix button order
2020-06-07 Add C_Cpp.default.includePath to VSCode settings.json
2020-06-07 Add .gitignore
2020-06-07 Fix all warnings
2020-06-07 Add servo control
2020-06-07 Fix missing break
2020-06-07 Simplify pwm computation, enable servo disable
2020-06-11 Implement DebugLink, some refactoring
2020-06-11 hw: apply pinout to the schematic
2020-06-11 hw: fix power circuit capacitors value
2020-06-11 hw: remove resistor between STM and ESP enable
2020-06-12 hw: add middle battery voltage (with overvoltage protection) to the power input terminal block (replaced by 3-pin)
2020-06-12 Remove v1.1 BSP preparation
2020-06-13 Re-implement _exit to handle abort()
2020-06-13 WIP: Add ultrasound
2020-06-14 Fix CdcUartTunnel, implement ESP32 boot sequences
2020-06-15 hw: fix DRV8833 packages (stop mask and orientation)
2020-06-15 hw: swap button 3 and 4, routing
2020-06-15 Refactor the Esp32Manager to emulate the ESP32 devkit more closely
2020-06-15 DebugLink fixups
2020-06-15 Switch ControlLink speed to 921600
2020-06-16 hw: routing
2020-06-16 Do not call DeInit in pinInit by default (fixes powering on)
2020-06-17 hw: routed
2020-06-17 hw: fix polygons and GND testpoint
2020-06-17 hw: minor fixes
2020-06-17 hw: move components away from pinheads
2020-06-17 hw: jumpers modified to match 0603 resistors
2020-06-17 hw: fix value of R74
2020-06-17 Use uintptr_t, log status queue oflow
2020-06-18 hw: move some resistors, because of silkscreen
2020-06-19 hw: update and fix silkscreens
    - fix position of labels
    - add testpoint labels
    - improve groups of text (separate columns in text labels)
    - add label for capacitors polarity
    - change layer from `tDocu` to `Document` for label in library `switch-omron.lbr`
2020-06-20 Add motor PWM control by @cednik
2020-06-21 hw: change outline layer of display modules
    - `diy-modules.lbr` - change outline layer from `tPlace` to `Document`
    - footprint `DISPLAY-OLED-128X32`
    - footprint `DISPLAY-OLED-128X64-I2C_W-HOLES`
2020-06-21 Add setBrake
2020-06-22 hw: fix position of origin in default jumper footprint
    - library `jumper.lbr` - `SJ2W_DEFAULT` - fix position of origin
    - update `RBCX.brd`
2020-06-22 hw: remove bottom mask under DRV8833s center pad
2020-06-22 hw: change size of holes for USBC connector
    - library `USB.lbr`
    - footprint `USB_C_8PIN` - change holes size from 0.35 mm to 0.30 mm to fit JLCPCB requirements
2020-06-22 Implement power off button
2020-06-24 Implement Esp32 watchdog
2020-06-24 FW test: add ADC, battery ADCy o working
2020-06-26 Use 100Hz motor loop, initialize pid
2020-06-27 Make motor loop more isochronous, use periodic dither, adjust default PID
2020-06-28 Properly init EN edge in Esp32Manager on startup
2020-06-29 Add motor state switching, tune back PID
2020-07-01 Remove DEBUG from motor loop
2020-07-03 Handle missing fw_ version tag
2020-07-05 hw: Release/manufacture version 1.1
    Summary:
    - fix USB-C connector - footprint `USB_C_8PIN` - change holes size from 0.35 mm to 0.30 mm to fit JLCPCB requirements
    - add USB-C auxiliary signals connector and soldering pads around USB connectors for better fixation
    - remove bottom mask and fix stop mask under DRV8833s centre pad
    - modify jumpers to match 0603 resistors size
    - fix position of origin in default jumper footprint for correct SMT
2020-07-05 Fix Queue and MessageBuffer wrapper's ISR yield handling
2020-07-05 Expand main task stack to 3KB to be safe
2020-07-05 Implement a softReset(); method
2020-07-06 Add commands to set motor power, velocity
2020-07-06 Use STM32's uid as serial number for the USB link
2020-07-06 Use INT16_MAX
2020-07-06 Simplify dither logic
2020-07-06 Add MutexWrapper and scoped_lock usage
2020-07-06 Simplify Regulator
2020-07-07 Don't give mutex on creation
2020-07-08 Add datasheets
2020-07-08 hw: remove old "parts (not updated).xlsx"
2020-07-08 doc: add CZ asembly manual for robot Robotka
2020-07-09 Handle USB events in IRQ rather than polling
    * The main loop is too slow for Windows drivers due to control
    messages decoding taking too long.
2020-07-10 Update BSP for v1.1, add more debug commands
    Closes #43
2020-07-11 Support building and flashing via sboot
    Updates #33
2020-07-11 Auto-reset RBCX into DFU on sboot upload
2020-07-11 Print detected version during build
2020-07-11 Add more delay for the debug uart btn check
2020-07-11 Fix post_dfu.py on Windows
2020-07-11 Add watchdog inhibit with debugger attached
2020-07-13 Add ENC filter
2020-07-13 Add homing/clearing of current position
2020-07-13 Fix member initialization in Motor
2020-07-13 Set target velocity=0 at position achieved instead of turning off
2020-07-13 Reinitialize motor to defaults at softreset, add MotorStat transaction
2020-07-15 Use better ramping logic
2020-07-15 Use sqrti
2020-09-19 hw: change version to v1.2
2020-09-19 hw: disconnect 3V3_EN and D11 (this connection prevents main step-down IM1 from startup)
2020-09-20 hw: update resistors R20-R23 value in parts_SMT.xlsx
2020-10-10 hw: add place for owner name
2020-10-11 hw: fixed iLed silkscreen
2020-10-12 hw: clean tNames and bNames
2020-10-12 hw: add pull-up resistors to encoders
2020-10-12 hw: add assembly variants
2020-10-12 hw: add D1 attributes
2020-10-12 hw: v1.2 snapshot
2021-04-05 Start LSE oscillator at clocks startup
2021-04-06 Enable RTC
2021-04-19 Revert velocity ramping motor changes
    They did not work well in real-world testing and we want the master
    to be useable.
    This reverts commit ca02e360475b70f186cf4639121ef47abeeff4ba.
    This reverts commit 5b80842b56ccd478ef0caa50ece7596251d0460a.
    This reverts commit d5262ff970676f4caf6ee55bf52c5202b1f619d8.
2021-04-19 Add RTC dispatch and alarm logic
2021-04-26 Init I2C
2021-04-26 I2C tests
2021-04-27 I2c ready to use
2021-04-30 I2c add CoprocStat for ESP
2021-04-30 Fix broken inclide
2021-05-01 Add OLED I2C driver
2021-05-02 Fix I2C devAddress
2021-05-02 OLED read requests from ESP
2021-05-02 Remove 'primary' uart historical mention
2021-05-05 Add full OLED support trought ESP
2021-05-08 MPU add basic commands for ESP
2021-05-11 Add nonblocking I2C experiment
2021-05-12 Fix include in Mpu header
2021-05-15 I2c add getCurrentTask - taskNotify and I2c mutex
2021-05-16 Remove HW 1.0 from CI
2021-07-22 Make i2c asynchronous
2021-07-23 Fix ESP reset by change i2c queue timeout, add i2c reset
2021-07-26 Add i2c error message
2021-07-26 Fix coproc link
2021-07-27 Fix MPU timer reinit
2022-10-13 Bump coproc comm for power coupling
2022-10-17 Simplify power coupling logic
2022-11-21 Remove stepdowns, Micro-USB; fixup region names
2023-02-08 Work in progress
2023-02-12 Labels on PCB
2023-02-12 Readme
2023-02-12 Production files
2023-02-15 Solder mask clearance
2023-02-18 Protective resistors for I2C on connectors
2023-02-27 Kuba issues - PCB
2023-03-04 Few small things
2023-03-25 Add images, fix doc
2023-03-25 Add open_in_new_tab.js
2023-03-26 Add views badges
2023-03-31 USB-DET level shifter
2023-05-02 Add support for CoprocStartup and EspWatchdogSettings messages
2023-05-30 Simplify the smart servo tunnel

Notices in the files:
hw/kicad_export/RBCX.kicad_pcb:
Creative Commons Attribution-ShareAlike 4.0 License
https://creativecommons.org/licenses/by-sa/4.0
